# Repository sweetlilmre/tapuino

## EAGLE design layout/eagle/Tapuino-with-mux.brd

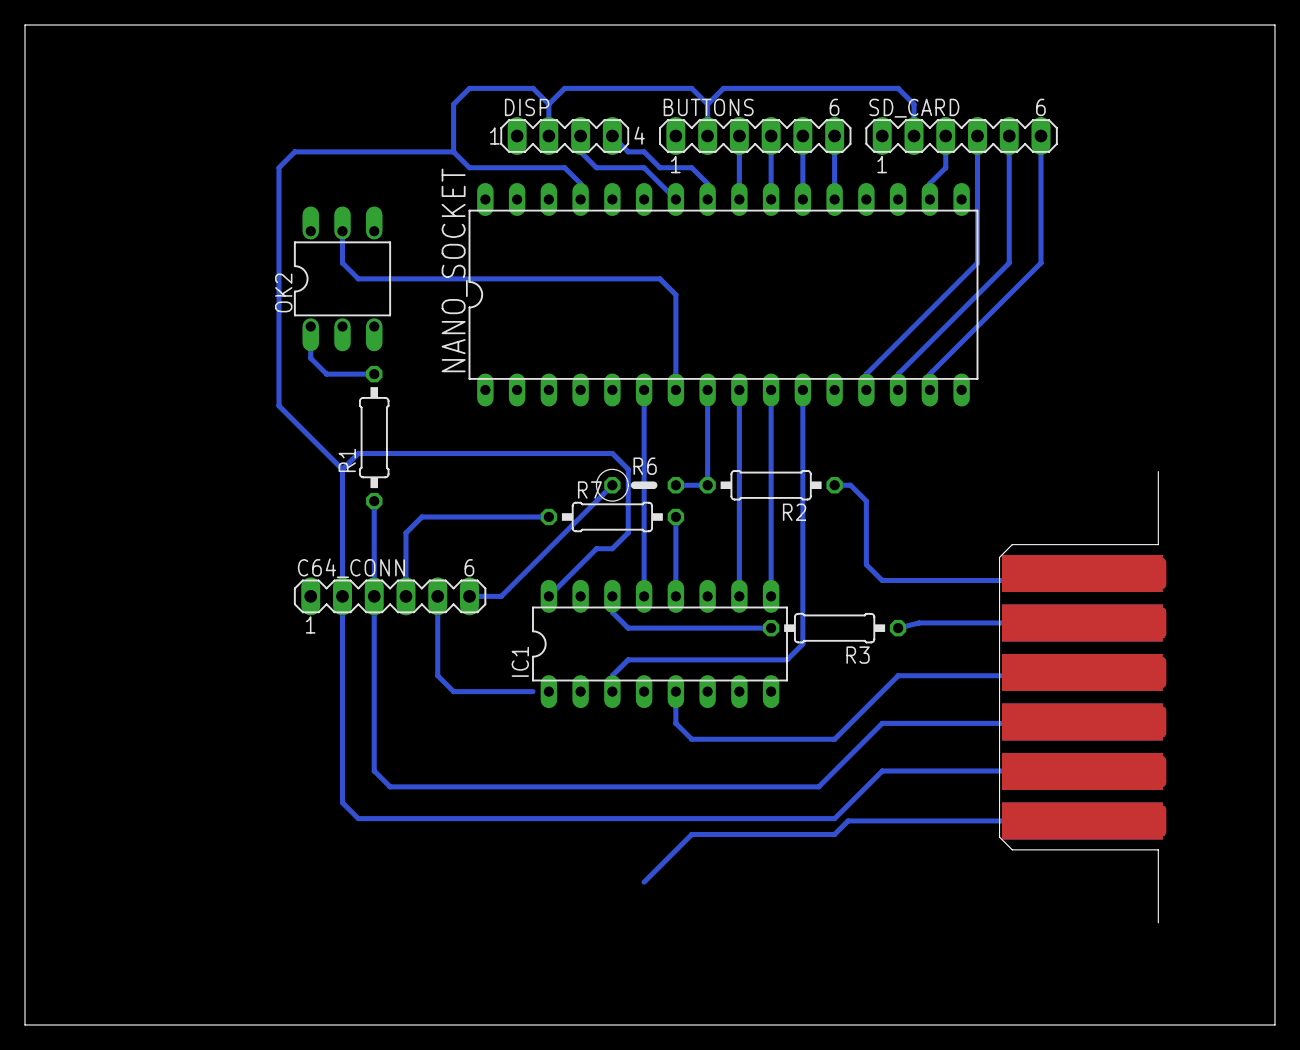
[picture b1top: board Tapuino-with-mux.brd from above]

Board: 2 copper layers, 100.0 x 80.0 mm, 13 parts (1 on the bottom side), 27 nets.

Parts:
BUTTONS: MA06-1
C64_CONN: MA06-1
CN1: C64_CASETTE_EDGE; C64_CASSETTE
DISP: MA04-1
IC1: 4052N; DIL16
NANO_SOCKET: DIL32
OK2: 4N25M; DIL06
R1: 430; 0207/10
R2, R3, R7: 0; 0207/10
R6: 0; 0207/5V
SD_CARD: MA06-1

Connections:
A0/BTN4: BUTTONS.6, NANO_SOCKET.21
A1/BTN3: BUTTONS.5, NANO_SOCKET.22
A2/BTN2: BUTTONS.4, NANO_SOCKET.23
A3/BTN1: BUTTONS.3, NANO_SOCKET.24
A4/SDA: DISP.4, NANO_SOCKET.25
A5/SCL: DISP.3, NANO_SOCKET.26
C64/READ: IC1.12, R7.2
C64/R_0OHM: C64_CONN.4, R7.1
D3/READ: IC1.13, NANO_SOCKET.6
D4/MCTRL: NANO_SOCKET.7, OK2.5
D5/SENSE: NANO_SOCKET.8, R2.2, R6.2
D5/S_0OHM: C64_CONN.6, R6.1
D5/S_0OHM2: CN1.6, R2.1
D6/CTRL1: IC1.10, NANO_SOCKET.9
D7/CTRL2: IC1.9, NANO_SOCKET.10
D8/WRITE: IC1.3, NANO_SOCKET.11
D10/SS: NANO_SOCKET.13, SD_CARD.4
D11/MOSI: NANO_SOCKET.14, SD_CARD.5
D12/MISO: NANO_SOCKET.15, SD_CARD.6
D13/SCK: NANO_SOCKET.18, SD_CARD.3
D/W_0OHM: CN1.5, R3.1
DAT/READ: CN1.4, IC1.5
DAT/WRITE: IC1.14, R3.2
GND: BUTTONS.1, C64_CONN.1, CN1.1, DISP.1, IC1.6, IC1.7, IC1.8, NANO_SOCKET.4, NANO_SOCKET.31, OK2.2, OK2.4, SD_CARD.1
MOTOR: C64_CONN.3, CN1.3, R1.1
OPTO-IN: OK2.1, R1.2
VCC: BUTTONS.2, C64_CONN.2, CN1.2, DISP.2, IC1.16, NANO_SOCKET.29, SD_CARD.2

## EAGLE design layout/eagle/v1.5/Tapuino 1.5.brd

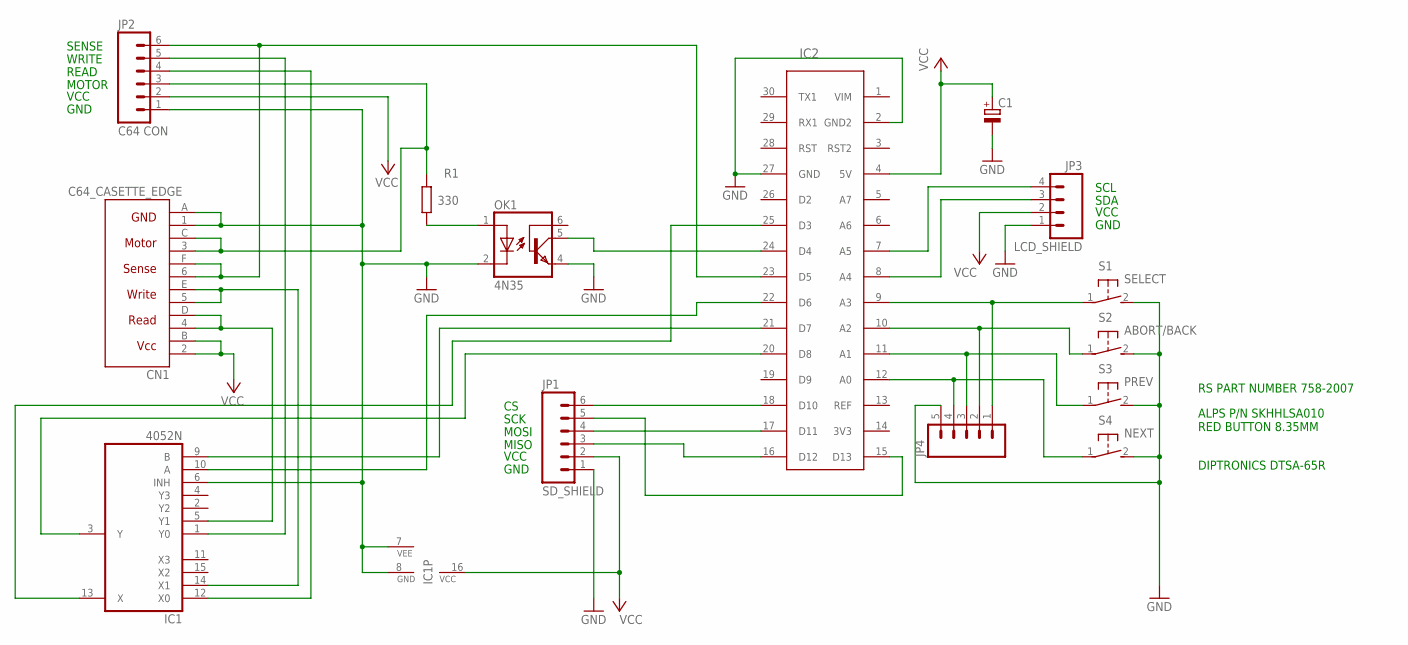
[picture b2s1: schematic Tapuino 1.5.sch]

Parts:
C1: CPOL-EUE2.5-6; E2,5-6
CN1: C64_CASETTE_EDGE; C64_CASSETTE
IC1: 4052N; DIL16
IC2: ARDUINO_NANO_V3; NANO_V3
JP1: SD_SHIELD; 1X06_LOCK_LONGPADS
JP2: C64 CON; 1X06_LOCK_LONGPADS
JP3: LCD_SHIELD; 1X04_LOCK_LONGPADS
JP4: M05LOCK_LONGPADS; 1X05_LOCK_LONGPADS
OK1: 4N35; DIL06
R1: 330; 0207/10
S1: SELECT; B3F-31XX
S2: ABORT/BACK; B3F-31XX
S3: PREV; B3F-31XX
S4: NEXT; B3F-31XX

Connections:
GND: C1.-, CN1.1 (GND1), CN1.A (GND2), IC1.6 (INH), IC1.7 (VEE), IC1.8 (GND), IC2.2 (GND2), IC2.27 (GND), JP1.1, JP2.1, JP3.1, JP4.5, OK1.2 (C), OK1.4 (EMI), S1.2 (S), S2.2 (S), S3.2 (S), S4.2 (S)
unnamed: IC2.16 (D12), JP1.3
unnamed: IC2.18 (D10), JP1.6
unnamed: IC2.15 (D13), JP1.5
unnamed: IC2.17 (D11), JP1.4
unnamed: IC2.7 (A5), JP3.4
unnamed: IC2.8 (A4), JP3.3
unnamed: IC2.9 (A3), JP4.1, S1.1
unnamed: OK1.1 (A), R1.1
unnamed: IC2.12 (A0), JP4.4, S4.1
unnamed: IC2.24 (D4), OK1.5 (COL)
unnamed: IC2.11 (A1), JP4.3, S3.1
unnamed: IC1.1 (Y0), JP2.5
unnamed: CN1.3 (MOTOR1), CN1.C (MOTOR2), JP2.3, R1.2
unnamed: IC1.3 (Y), IC2.20 (D8)
unnamed: IC1.12 (X0), JP2.4
unnamed: CN1.6 (SENSE1), CN1.F (SENSE2), IC2.23 (D5), JP2.6
unnamed: IC1.13 (X), IC2.25 (D3)
unnamed: CN1.4 (READ1), CN1.D (READ2), IC1.5 (Y1)
unnamed: IC1.9 (B), IC2.21 (D7)
unnamed: CN1.5 (WRITE1), CN1.E (WRITE2), IC1.14 (X1)
unnamed: IC1.10 (A), IC2.22 (D6)
unnamed: IC2.10 (A2), JP4.2, S2.1
VCC: C1.+, CN1.2 (VCC1), CN1.B (VCC2), IC1.16 (VCC), IC2.4 (5V), JP1.2, JP2.2, JP3.2

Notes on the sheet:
SCK
MOSI
MISO
VCC
GND
SCL
SDA
SENSE
WRITE
READ
MOTOR
RS PART NUMBER 758-2007
ALPS P/N SKHHLSA010 RED BUTTON 8.35MM
DIPTRONICS DTSA-65R

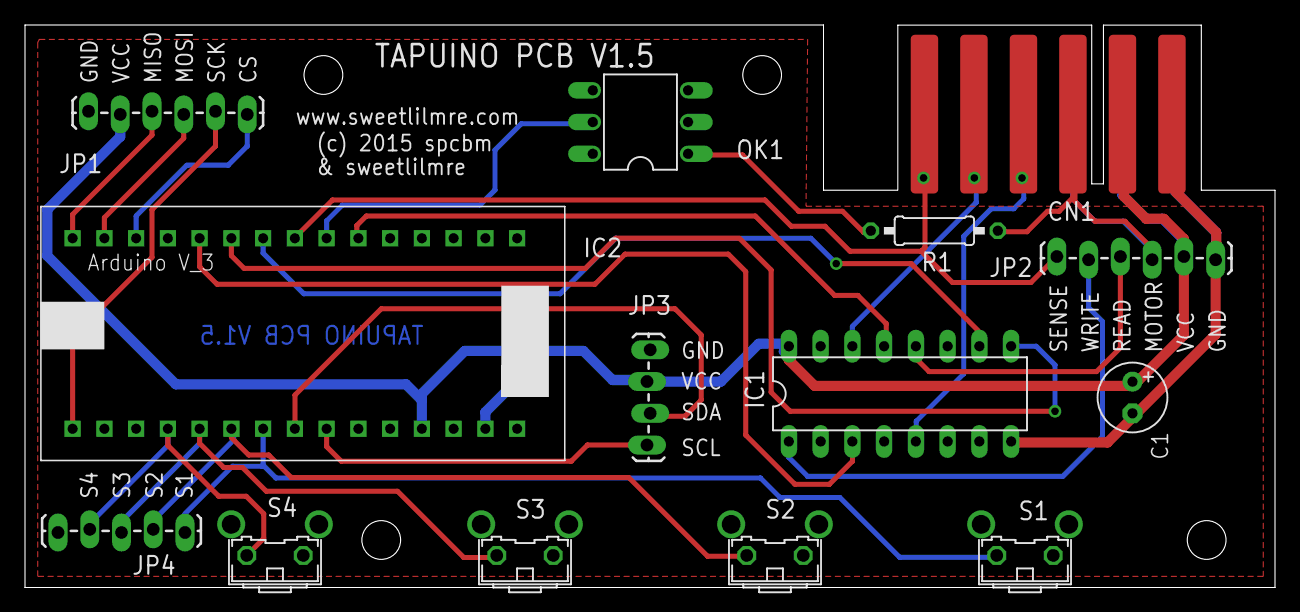
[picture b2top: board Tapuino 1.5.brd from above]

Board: 2 copper layers, 100.0 x 45.0 mm, 14 parts (0 on the bottom side), 24 nets.

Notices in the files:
layout/eagle/v1.5/Tapuino 1.5.brd:
(c) 2015 spcbm
parts and their libraries:
SparkFun: Licensing: CC v3.0 Share-Alike You are welcome to use this library for commercial purposes.
